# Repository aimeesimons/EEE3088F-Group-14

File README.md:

# EEE3088F-Group-14
Aimee Simons, Ashik John, Kudzi Kadzimu

1. 	Final Project has all the latest kicad files, 
	FullSchematic is the file with all modules combined

2.	PCB Submission contains PCB Files submitted for manufacture

3.	Report Submission contains weekly design assignment reports

4.	Miscellaneous files contains all other files used in the project, 
	THE FILES MAY NOT BE UP TO DATE WITH THE FINAL SUBMISSION!

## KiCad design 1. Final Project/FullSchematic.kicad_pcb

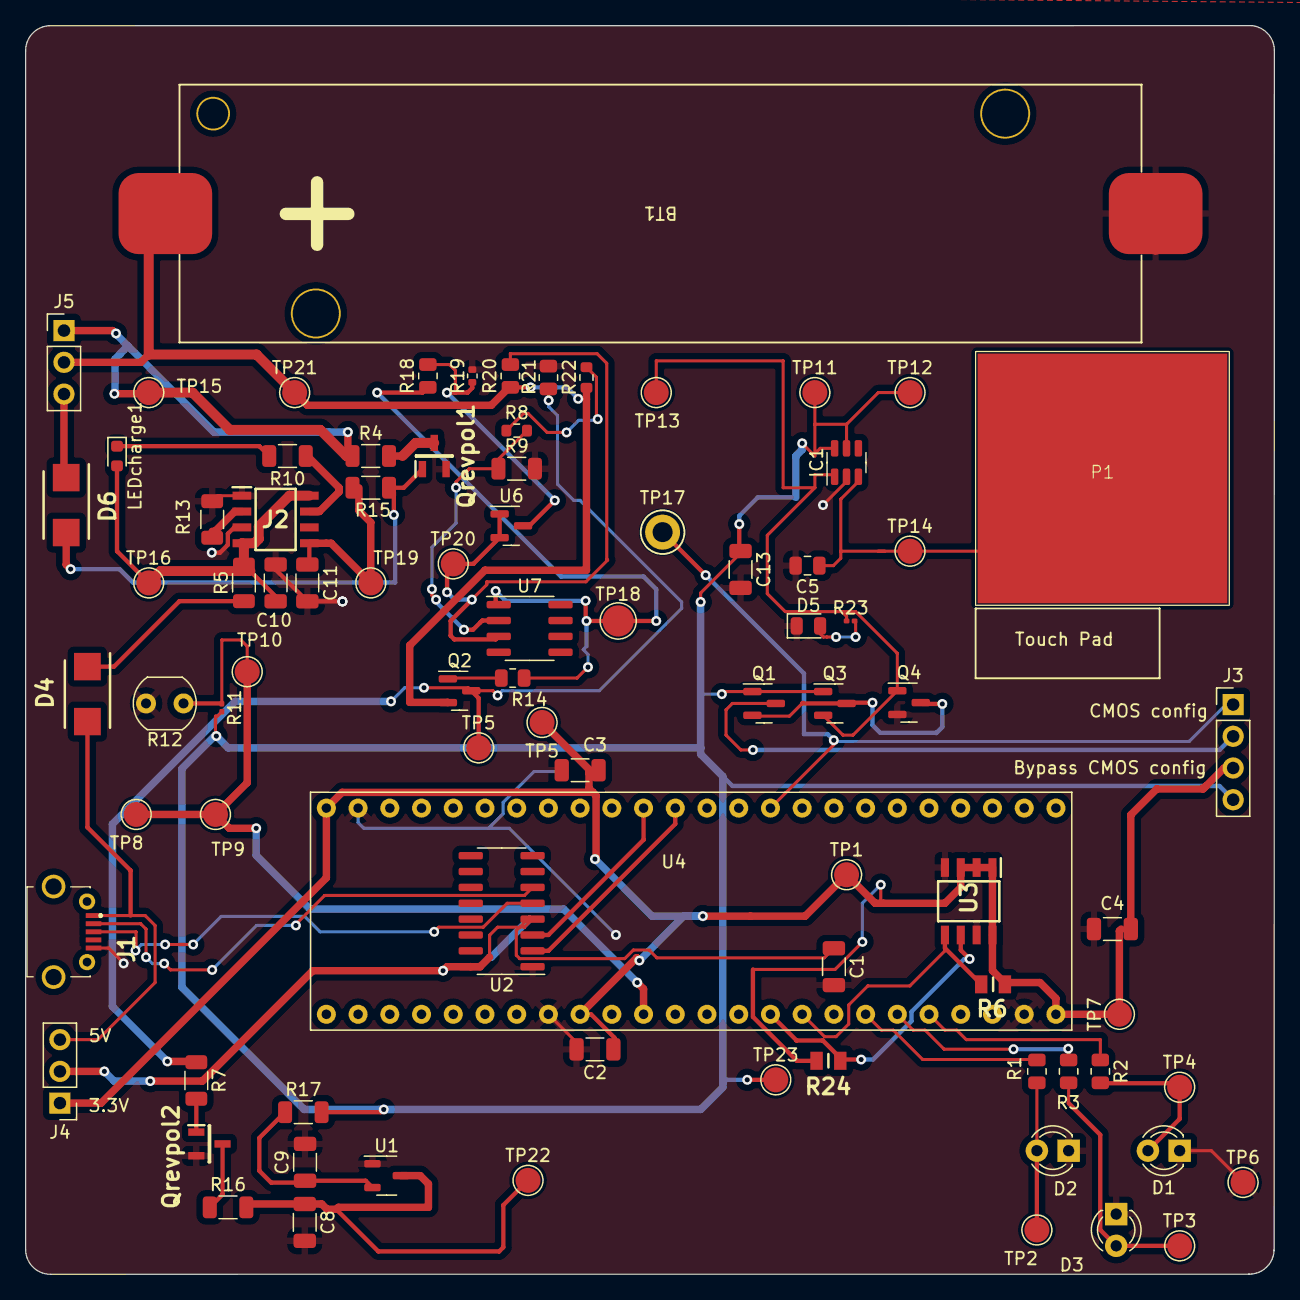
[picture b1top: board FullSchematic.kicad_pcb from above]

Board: 2 copper layers, 100.0 x 100.0 mm, 85 parts (0 on the bottom side), 46 nets.

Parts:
BT1: Battery_Cell; 18650_Holder_SMD
C1, C2, C3, C4, C13: 100nF; C_1206_3216Metric
C5: 20pF; C_0805_2012Metric
C8, C9, C10, C11: 10uF; C_1206_3216Metric
D1, D2, D3: LED; LED_D3.0mm_IRBlack
D4, D6: Schottky - 0.21@1A; Schottky Diode
D5: LED; LED_0805_2012Metric
IC1: TTP223E-BA6; SOT-23-6
J1: USB_B_Micro; MICROXNJ
J2: TP4056; SOIC127P600X175-8N
J3: Conn_01x04_Pin; PinHeader_1x04_P2.54mm_Vertical
J4, J5: Conn_01x03_Pin; PinHeader_1x03_P2.54mm_Vertical
LEDcharge1: RED; LED_0603_1608Metric
P1: Touch Pad
Q1, Q2, Q3: SI2301CDS; SOT-23
Q4: 2N7002; SOT-23
Qrevpol1, Qrevpol2: PMOS; Si2323
R1, R2, R3: 270R; R_0805_2012Metric
R4, R5, R7, R15, R16, R17: 0; R_1206_3216Metric
R6, R24: 4.7k; RESC2013X65N
R8, R22: 2M; R_0603_1608Metric
R9: 2.5M; R_1206_3216Metric
R10: 1k; R_1206_3216Metric
R11: 10k; R_0201_0603Metric
R12: LDR03; R_LDR_5.0x4.1mm_P3mm_Vertical
R13: 2k; R_1206_3216Metric
R14: 1M; R_0805_2012Metric
R18: 10M; R_0805_2012Metric
R19: 150k; R_0402_1005Metric
R20: 2.05M; R_0805_2012Metric
R21: 100k; R_0805_2012Metric
R23: 150R; R_0201_0603Metric
TP1, TP2, TP3, TP4, TP5, TP5#2, TP6, TP7, TP8, TP9, TP10, TP11, TP12, TP13, TP14, TP15, TP16, TP19, TP20, TP21, TP22, TP23: TestPoint; TestPoint_Pad_D2.0mm
TP17: TestPoint; TestPoint_Keystone_5005-5009_Compact
TP18: TestPoint; TestPoint_Pad_D2.5mm
U1: XC6206P332MR; SOT-23-3
U2: CH340C; SOIC-16_3.9x9.9mm_P1.27mm
U3: AT24C256C; SOIC127P600X175-8N
U4: STM32F051C6T6
U6: CJ432; SOT-23
U7: NE5532; SOIC-8_3.9x4.9mm_P1.27mm

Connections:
/Microcontroller/3.3V: C2.1, C3.1, C4.1, J3.3, J4.1, R6.1, R24.1, TP1.1, TP5#2.1, TP7.1, U3.1 (A0), U3.2 (A1), U3.3 (A2), U3.8 (VCC), U4.9 (V+), U4.24 (V+), U4.48 (V+)
/Microcontroller/5V: D4.2 (A), J1.1 (VBUS), J4.3
/Microcontroller/LDR_sensor: R11.2, R12.1, TP8.1, TP9.1, TP10.1, U4.11 (PA1)
/Microcontroller/Rx: U2.2 (TXD), U4.37 (PA14)
/Microcontroller/SCL: R24.2, U3.6 (SCL), U4.15 (PA5)
/Microcontroller/SDA: R6.2, U3.5 (SDA), U4.16 (PA6)
/Microcontroller/T_sensor: J3.1, TP17.1, U4.34 (PA13)
/Microcontroller/Tx: U2.3 (RXD), U4.38 (PA15)
/Microcontroller/out1: R1.1, U4.18 (PB0)
/Microcontroller/out2: R2.1, U4.20 (PB2)
/Microcontroller/out3: R3.1, U4.19 (PB1)
/Output of Touch Sensor: IC1.1 (Q), Q3.2 (G), Q4.1 (G), R23.1, TP13.1
/Pin 2: J3.2, Q1.3 (S)
/Power Module/Charging/Vbat: BT1.1 (+), J5.2, Q2.2 (S), R20.1, R22.1, TP21.1
/Power Module/Charging/Vin: C10.1, J2.4 (VCC4), J2.8 (CE), LEDcharge1.2 (A), R5.2, TP16.1
/Power Module/Regulating/Vbat: Q2.3 (D), R7.1, R21.1, TP5.1
/Power Module/Regulating/Vin: C8.1, R16.2, TP22.1, U1.3 (VI)
/Vboard: C13.1, IC1.5 (VDD), IC1.6 (TOG), J3.4, Q1.1 (D), Q3.1 (D), R11.1, R17.2, TP11.1, TP12.1, TP23.1
GND: BT1.2 (-), C1.2, C2.2, C3.2, C4.2, C5.2, C8.2, C9.2, C10.2, C11.2, C13.2, D1.1 (K), D2.1 (K), D3.1 (K), D5.1 (K), IC1.2 (VSS), J1.5 (GND), J2.1 (TEMP1), J2.3 (GND_3), Q4.2 (S), Qrevpol1.2 (G), Qrevpol2.2 (G), R9.2, R12.2, R13.1, R19.2, R21.2, TP6.1, U1.1 (GND), U2.1 (GND), U3.4 (GND), U3.7 (WP), U4.8 (GND), U4.23 (GND), U4.47 (GND)
unnamed: C1.1, J4.2, U2.4 (V3), U2.16 (VCC)
unnamed: D1.2 (A), R2.2, TP4.1
unnamed: D2.2 (A), R1.2, TP2.1
unnamed: D3.2 (A), R3.2, TP3.1
unnamed: D4.1 (K), R5.1
unnamed: D5.2 (A), R23.2
unnamed: D6.2 (A), Qrevpol1.1 (D), R15.2
unnamed: D6.1 (K), J5.3
unnamed: C5.1, IC1.3 (I), P1.Touch Pad1, TP14.1
unnamed: J1.3 (D+), U2.5 (UD+)
unnamed: J1.2 (D-), U2.6 (UD-)
unnamed: C11.1, J2.5 (BAT), R15.1, TP19.1
unnamed: J2.2 (PROG2), R13.2
unnamed: J2.7 (~CHRG), R10.1
unnamed: J5.1, R4.1, TP15.1
unnamed: LEDcharge1.1 (K), R10.2
unnamed: Q1.2 (G), Q3.3 (S), Q4.3 (D)
unnamed: Q2.1 (G), R14.1
unnamed: Qrevpol1.3 (S), R4.2
unnamed: Qrevpol2.1 (D), R7.2
unnamed: Qrevpol2.3 (S), R16.1
unnamed: R14.2, R18.1, TP18.1, U7.1
unnamed: R8.1, R22.2
unnamed: C9.1, R17.1, U1.2 (VO)
unnamed: R18.2, R19.1, U6.3 (A)
unnamed: R20.2, TP20.1, U6.1 (REF), U6.2 (K), U7.3 (+)
unnamed: R8.2, R9.1, U7.2 (-)

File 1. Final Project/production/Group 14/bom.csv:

Designator,Footprint,Quantity,Value,LCSC Part #
BT1,18650_Holder_SMD,1,Battery_Cell,
"C1, C2, C3, C4",1206,4,100nF,C24497
"C10, C11, C8, C9",0603,4,10uF,C1691
C13,C_Disc_D4.3mm_W1.9mm_P5.00mm,1,100nF,C409812
C5,C_Disc_D4.7mm_W2.5mm_P5.00mm,1,20pF,C123152
"D1, D2, D3",LED_D3.0mm_IRBlack,3,LED,C54142
"D4, D6",Schottky Diode,2,Schottky - 0.21@1A,C413465
D5,0201,1,LED,C165982
IC1,SOT-563,1,TTP223E-BA6,C1693666
J1,MICROXNJ,1,USB_B_Micro,C404969
J2,SOIC127P600X175-8N,1,TP4056,C382139
"J3, J4, J5",PinHeader_1x03_P2.54mm_Vertical,3,Conn_01x03_Pin,
LEDcharge1,0603,1,RED,C2286
P1,Touch Pad,1,Touch Pad,
"Q1, Q2, Q3",SOT-23,3,IRLML6402,C518785
Q4,SOT-23,1,2N7002,C111971
"Qrevpol1, Qrevpol2",Si2323,2,PMOS,C5337196
"R1, R2, R3",1206,3,270R,C4466
R10,1206,1,1k,C4410
R11,0201,1,180,C22828
R12,R_LDR_5.0x4.1mm_P3mm_Vertical,1,LDR03,C125627
R13,1206,1,2k,C17944
R14,0805,1,1M,C416080
"R15, R16, R17, R4, R5, R7",1206,6,0,C17888
R18,0805,1,10M,C26108
R19,0402,1,150k,C429049
R20,0805,1,2.05M,C784207
R21,0805,1,100k,C465471
"R22, R8",0603,2,2M,C465466
R23,0201,1,150R,C136932
R6,RESC2013X65N,1,4700,C23162
R9,1206,1,2.5M,C508414
"TP1, TP10, TP11, TP12, TP13, TP14, TP15, TP16, TP19, TP2, TP20, TP21, TP22, TP23, TP3, TP4, TP5_2, TP5, TP6, TP7, TP8, TP9",TestPoint_Pad_D2.0mm,22,TestPoint,
TP17,TestPoint_Keystone_5005-5009_Compact,1,TestPoint,
TP18,TestPoint_Pad_D2.5mm,1,TestPoint,
U1,SOT-223,1,LM1117-3.3,C126027
U2,SOIC-16_3.9x9.9mm_P1.27mm,1,CH340C,C84681
U3,SOIC127P600X175-8N,1,24LC64,C511260
U4,STM32F051C6T6,1,STM32F051C6T6,
U5,SOIC127P600X175-8N,1,OP184,C690879
U6,SOT-23,1,CJ432,C8499

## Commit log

2023-03-04 Added Word Doc to Repo
2023-03-04 Added Sensor Files
2023-03-04 Drew up draft schematic for analogue sensor
2023-03-04 Created Bill Spreadsheet
2023-03-04 Design Proposal Doc
2023-03-04 Creating Digital Sensor Schematic
2023-03-05 added component values
2023-03-05 finalising draft schematics
2023-03-05 Not needeed
2023-03-06 Convert to excel spreadsheet
2023-03-06 Add files via upload
    Convert to spreadsheet
2023-03-06 Add files via upload
    Convert to excel spreadsheet
2023-03-09 Updated schematics
2023-03-10 DataSheet
2023-03-11 Combining Schemtics
2023-03-11 global changes
2023-03-12 Combing all schematics
2023-03-12 Moved to full schematic folder
2023-03-13 completed and generated BOM
2023-03-14 added power flags
2023-03-15 updated footprints
2023-03-16 added more footprints
2023-03-16 Before merge-aimee
2023-03-16 Merging g to be committed:
2023-03-16 Corrected errors
2023-03-16 committed
2023-03-16 tried to go to previous version
2023-03-16 almost there
2023-03-16 Aimee
2023-03-16 resetting
2023-03-16 Opening MicroController
2023-03-16 Microcontroller included
2023-03-16 adding of all footprints
2023-03-17 updated schematics and footprints
2023-03-18 updated schematic and footprints
2023-03-18 connected sensors adnd created touch pad
2023-03-19 connected microcontroller
2023-03-20 finalised pcb design
2023-03-20 copied correct file
2023-03-21 generated Gerber files
2023-03-30 Added uvlo circuit
2023-03-31 updated microcontroller BOM and added qr code to b.silk
2023-03-31 Confirmed part numbers and prices
2023-04-02 corrected connection
2023-04-03 Checked part #s, prices, footprints
2023-04-03 Final Board
2023-04-04 generated files
2023-04-08 Decreased Price
2023-04-13 Uploaded final board design
2023-04-13 Organised repo, added instructions to ReadMe
2023-04-24 updated submission folders
2023-04-24 made sure git repo is up to date
